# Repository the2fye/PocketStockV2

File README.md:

# PocketStockV2
ESP32-based dual OLED stock ticker displaying real-time market data

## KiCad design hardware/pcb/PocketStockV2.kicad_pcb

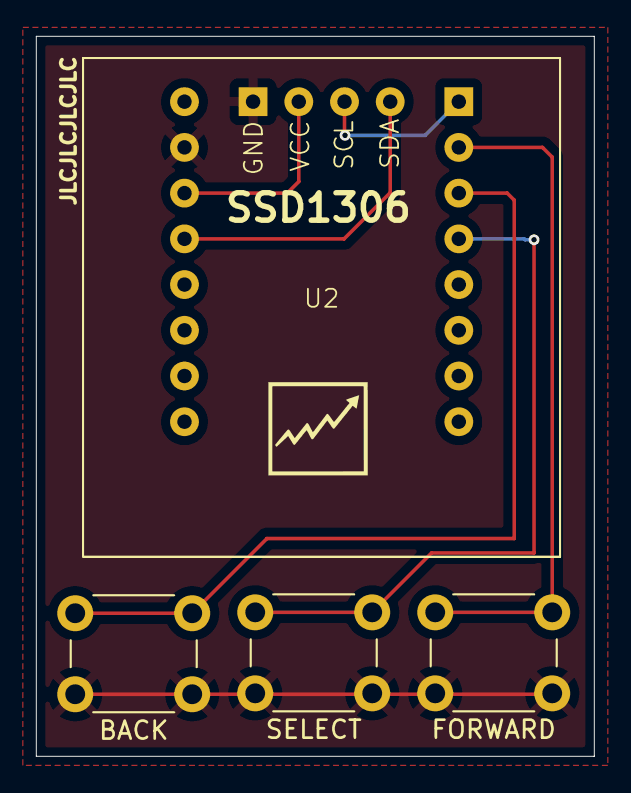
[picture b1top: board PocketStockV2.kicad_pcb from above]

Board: 4 copper layers, 31.0 x 40.0 mm, 5 parts (1 on the bottom side), 7 nets.

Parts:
BACK: SW_back; SW_PUSH_6mm
FORWARD: SW_Forward; SW_PUSH_6mm
SELECT: SW_Select; SW_PUSH_6mm
U1: C3_SuperMIni; ESP_32_C3_SuperMini
U2: SSD1306

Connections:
+3.3V: U1.11 (3.3V), U2.2 (VCC)
GND: BACK.1, FORWARD.1, SELECT.1, U1.10 (GND), U2.1 (GND)
unnamed: U1.12 (GPIO4), U2.4 (SDA)
unnamed: U1.1 (GPIO5), U2.3 (SCL)
unnamed: FORWARD.2, U1.2 (GPIO6)
unnamed: BACK.2, U1.3 (GPIO7)
unnamed: SELECT.2, U1.4 (GPIO8)

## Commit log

2026-03-23 Initialize project structure for PocketStock V2
2026-03-23 Add placeholder files to track empty directories
2026-03-23 Organize hardware folder with PCB, schematics, and BOM; add supporting data and new firmware file
2026-03-23 Add .DS_Store to .gitignore and remove system files from repository
2026-03-24 Remove placeholder files from project directories
